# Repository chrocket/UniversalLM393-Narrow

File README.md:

# UniversalLM393-Narrow
Photodiode sensor board, 0.4905 inches wide, for RocketTrig

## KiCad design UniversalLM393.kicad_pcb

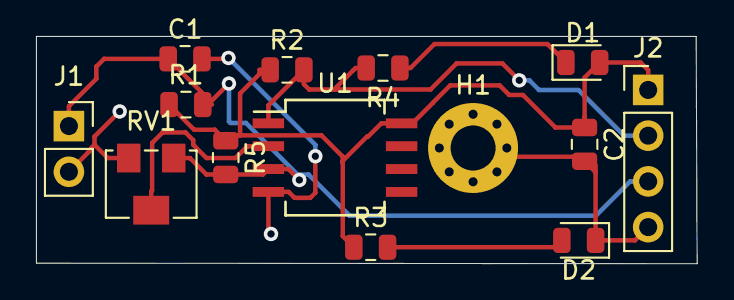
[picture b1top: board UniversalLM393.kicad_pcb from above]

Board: 2 copper layers, 36.7 x 12.6 mm, 14 parts (0 on the bottom side), 7 nets.

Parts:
C1, C2: 100 nf; C_0805_2012Metric
D1, D2: LED; D_0805_2012Metric
H1: MountingHole_2.5mm_Pad_Via
J1: PinSocket_1x02_P2.54mm_Vertical
J2: PinHeader_1x04_P2.54mm_Vertical
R1, R2: 10K; R_0805_2012Metric
R3: 787; R_0805_2012Metric
R4: 1K; R_0805_2012Metric
R5: 440; R_0805_2012Metric
RV1: 10K; Potentiometer_Bourns_3214W_Vertical
U1: LM393; SO-8_5.3x6.2mm_P1.27mm

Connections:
DO: J2.2, R2.2, R4.2, U1.1
GND: C1.2, C2.2, D2.1, H1.1, J1.2, J2.4, RV1.3, U1.4
unnamed: D1.1, R4.1
unnamed: D2.2, R3.2
unnamed: RV1.2, U1.2
Signal: C1.1, J1.1, J2.3, R1.2, R5.2, RV1.1, U1.3
VCC: C2.1, D1.2, J2.1, R1.1, R2.1, R3.1, R5.1, U1.8

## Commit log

2020-06-02 Add files via upload
    Initial version and PCB
